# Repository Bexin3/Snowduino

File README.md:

# Snowduino
Want to get your own PCB? These files are all you need (untested)

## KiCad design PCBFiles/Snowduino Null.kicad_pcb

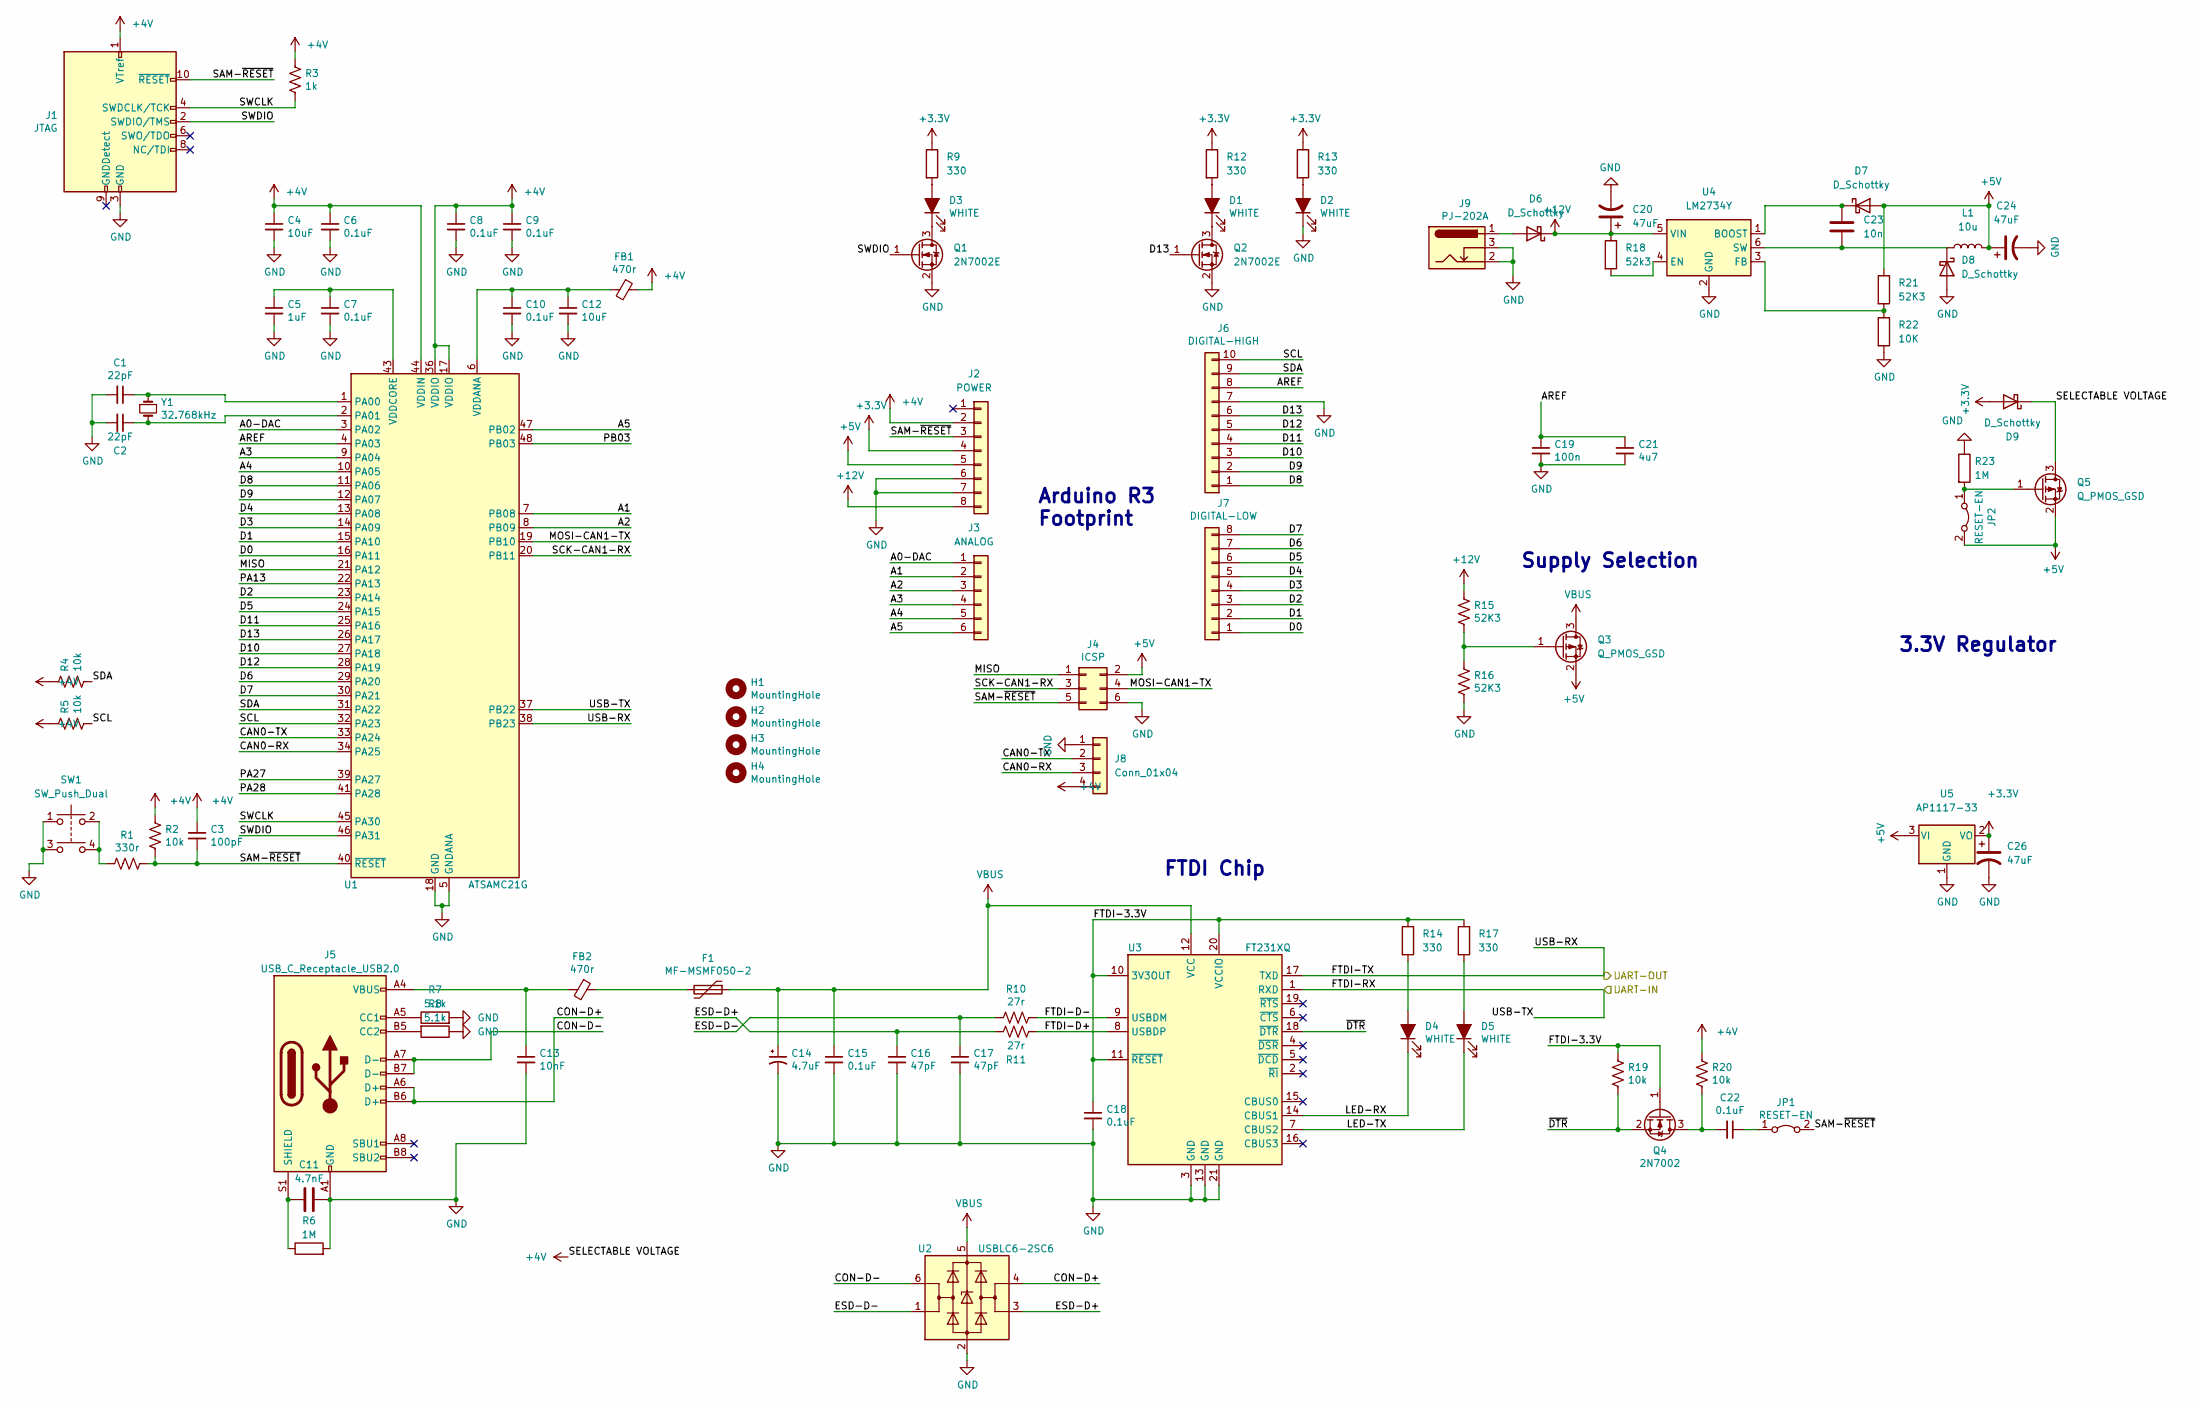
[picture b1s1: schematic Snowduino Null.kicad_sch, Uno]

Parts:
C1, C2: 22pF; C_0603_1608Metric
C3: 100pF; C_0603_1608Metric
C4, C12: 10uF; C_0805_2012Metric
C5: 1uF; C_0805_2012Metric
C6, C7, C8, C9, C10, C15, C18, C22: 0.1uF; C_0603_1608Metric
C11: 4.7nF; C_0603_1608Metric
C13: 10nF; C_0603_1608Metric
C14: 4.7uF; C_0805_2012Metric
C16, C17: 47pF; C_0603_1608Metric
C19: 100n; C_0603_1608Metric
C20, C24, C26: 47uF; CP_Elec_6.3x3.9
C21: 4u7; C_0603_1608Metric
C23: 10n; C_0603_1608Metric
D1, D2, D3, D4, D5: WHITE; LED_0603_1608Metric
D6, D7, D8: D_Schottky; D_SOD-123F
D9: D_Schottky; D_SOD-323
F1: MF-MSMF050-2; Fuse_1812_4532Metric
FB1: 470r; R_0603_1608Metric
FB2: 470r; R_0603_1608Metric; Part Number BLM18PG471SN1; Digikey PN 490-5223-1-ND
H1, H2, H3, H4: MountingHole; MountingHole_3.2mm_M3
J1: JTAG; PinHeader_2x05_P1.27mm_Vertical
J2: POWER; PinSocket_1x08_P2.54mm_Vertical
J3: ANALOG; PinSocket_1x06_P2.54mm_Vertical
J4: ICSP; PinHeader_2x03_P2.54mm_Vertical
J5: USB_C_Receptacle_USB2.0; USB_C_Receptacle_HRO_TYPE-C-31-M-12
J6: DIGITAL-HIGH; PinSocket_1x10_P2.54mm_Vertical
J7: DIGITAL-LOW; PinSocket_1x08_P2.54mm_Vertical
J8: Conn_01x04; PinHeader_1x04_P2.54mm_Vertical
J9: PJ-202A; DC005G25A20
JP1: RESET-EN; SolderJumper-2_P1.3mm_Bridged_RoundedPad1.0x1.5mm
JP2: RESET-EN; PinHeader_1x02_P1.27mm_Vertical
L1: 10u; L_6.3x6.3_H3
Q1, Q2: 2N7002E; SOT-23
Q3, Q5: Q_PMOS_GSD; SOT-23
Q4: 2N7002; SOT-23
R1: 330r; R_0603_1608Metric
R2, R4, R5, R19, R20: 10k; R_0603_1608Metric
R3: 1k; R_0603_1608Metric
R6, R23: 1M; R_0603_1608Metric
R7, R8: 5.1k; R_0603_1608Metric
R9, R12, R13, R14, R17: 330; R_0603_1608Metric
R10, R11: 27r; R_0603_1608Metric
R15, R16, R21: 52K3; R_0603_1608Metric
R18: 52k3; R_0603_1608Metric
R22: 10K; R_0603_1608Metric
SW1: SW_Push_Dual; PTS641SM31SMTR2LFS
U1: ATSAMC21G; TQFP-48_7x7mm_P0.5mm
U2: USBLC6-2SC6; SOT-23-6
U3: FT231XQ; QFN-20-1EP_4x4mm_P0.5mm_EP2.5x2.5mm
U4: LM2734Y; TSOT-23-6
U5: AP1117-33; SOT-223-3_TabPin2
Y1: 32.768kHz; Crystal_SMD_MicroCrystal_CC7V-T1A-2Pin_3.2x1.5mm

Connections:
+3V3: C26.1, D9.2 (A), J2.4, R9.1, R12.1, R13.1, U5.2 (VO)
+4V: C3.1, C4.1, C6.1, C8.1, C9.1, D9.1 (K), FB1.1, J1.1 (VTref), J2.2, J8.4, Q5.3 (D), R2.2, R3.1, R4.2, R5.2, R20.1, U1.17 (VDDIO), U1.36 (VDDIO), U1.44 (VDDIN)
+5V: C24.1, D7.2 (A), J2.5, J4.2, JP2.2 (B), L1.2, Q3.2 (S), Q5.2 (S), R21.1, U5.3 (VI)
+12V: C20.1, D6.1 (K), J2.8, R15.1, R18.1, U4.5 (VIN)
/A0-DAC: J3.1, U1.3 (PA02)
/A1: J3.2, U1.7 (PB08)
/A2: J3.3, U1.8 (PB09)
/A3: J3.4, U1.9 (PA04)
/A4: J3.5, U1.10 (PA05)
/A5: J3.6, U1.47 (PB02)
/AREF: C19.1, C21.1, J6.8, U1.4 (PA03)
/CAN0-RX: J8.3, U1.34 (PA25)
/CAN0-TX: J8.2, U1.33 (PA24)
/CON-D+: J5.A6 (D+), J5.B6 (D+), U2.4 (I/O2)
/CON-D-: J5.A7 (D-), J5.B7 (D-), U2.6 (I/O1)
/D0: J7.1, U1.16 (PA11)
/D1: J7.2, U1.15 (PA10)
/D2: J7.3, U1.23 (PA14)
/D3: J7.4, U1.14 (PA09)
/D4: J7.5, U1.13 (PA08)
/D5: J7.6, U1.24 (PA15)
/D6: J7.7, U1.29 (PA20)
/D7: J7.8, U1.30 (PA21)
/D8: J6.1, U1.11 (PA06)
/D9: J6.2, U1.12 (PA07)
/D10: J6.3, U1.27 (PA18)
/D11: J6.4, U1.25 (PA16)
/D12: J6.5, U1.28 (PA19)
/D13: J6.6, Q2.1 (G), U1.26 (PA17)
/ESD-D+: C16.1, R11.2, U2.3 (I/O2)
/ESD-D-: C17.1, R10.2, U2.1 (I/O1)
/FTDI-3.3V: C18.1, Q4.1 (G), R14.1, R17.1, R19.1, U3.10 (3V3OUT), U3.11 (~RESET), U3.20 (VCCIO)
/FTDI-D+: R11.1, U3.8 (USBDP)
/FTDI-D-: R10.1, U3.9 (USBDM)
/FTDI-RX: U1.37 (PB22), U3.1 (RXD)
/FTDI-TX: U1.38 (PB23), U3.17 (TXD)
/LED-RX: D4.1 (K), U3.14 (CBUS1)
/LED-TX: D5.1 (K), U3.7 (CBUS2)
/MISO: J4.1, U1.21 (PA12)
/MOSI-CAN1-TX: J4.4, U1.19 (PB10)
/PA13: U1.22 (PA13)
/PA27: U1.39 (PA27)
/PA28: U1.41 (PA28)
/PB03: U1.48 (PB03)
/SAM-~RESET: C3.2, J1.10 (~RESET), J2.3, J4.5, JP1.2 (B), R1.1, R2.1, U1.40 (~RESET)
/SCK-CAN1-RX: J4.3, U1.20 (PB11)
/SCL: J6.10, R5.1, U1.32 (PA23)
/SDA: J6.9, R4.1, U1.31 (PA22)
/SWCLK: J1.4 (SWDCLK/TCK), R3.2, U1.45 (PA30)
/SWDIO: J1.2 (SWDIO/TMS), Q1.1 (G), U1.46 (PA31)
/~DTR: Q4.2 (S), R19.2, U3.18 (~DTR)
GND: C1.2, C2.2, C4.2, C5.2, C6.2, C7.2, C8.2, C9.2, C10.2, C11.1, C12.2, C13.2, C14.2, C15.2, C16.2, C17.2, C18.2, C19.2, C20.2, C21.2, C24.2, C26.2, D2.1 (K), D8.2 (A), J1.3 (GND), J1.5 (GND), J2.6, J2.7, J4.6, J5.A1 (GND), J5.A12 (GND), J5.B1 (GND), J5.B12 (GND), J6.7, J8.1, J9.2, J9.3, Q1.2 (S), Q2.2 (S), R6.2, R7.2, R8.1, R16.2, R22.2, R23.1, SW1.1, SW1.3, U1.5 (GNDANA), U1.18 (GND), U1.35 (GND), U1.42 (GND), U2.2 (GND), U3.3 (GND), U3.13 (GND), U3.21 (GND), U4.2 (GND), U5.1 (GND)
unnamed: C1.1, U1.1 (PA00), Y1.1
unnamed: C2.1, U1.2 (PA01), Y1.2
unnamed: C5.1, C7.1, U1.43 (VDDCORE)
unnamed: C10.1, C12.1, FB1.2, U1.6 (VDDANA)
unnamed: C11.2, J5.S1 (SHIELD), R6.1
unnamed: C13.1, FB2.2, J5.A4 (VBUS), J5.A9 (VBUS), J5.B4 (VBUS), J5.B9 (VBUS)
unnamed: C22.1, JP1.1 (A)
unnamed: C22.2, Q4.3 (D), R20.2
unnamed: C23.1, D7.1 (K), U4.1 (BOOST)
unnamed: C23.2, D8.1 (K), L1.1, U4.6 (SW)
unnamed: D1.1 (K), Q2.3 (D)
unnamed: D1.2 (A), R12.2
unnamed: D2.2 (A), R13.2
unnamed: D3.1 (K), Q1.3 (D)
unnamed: D3.2 (A), R9.2
unnamed: D4.2 (A), R14.2
unnamed: D5.2 (A), R17.2
unnamed: D6.2 (A), J9.1
unnamed: F1.2, FB2.1
unnamed: J5.A5 (CC1), R7.1
unnamed: J5.B5 (CC2), R8.2
unnamed: JP2.1 (A), Q5.1 (G), R23.2
unnamed: Q3.1 (G), R15.2, R16.1
unnamed: R1.2, SW1.2, SW1.4
unnamed: R18.2, U4.4 (EN)
unnamed: R21.2, R22.1, U4.3 (FB)
VBUS: C14.1, C15.1, F1.1, Q3.3 (D), U2.5 (VBUS), U3.12 (VCC)

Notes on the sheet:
FTDI Chip
Arduino R3 Footprint
Supply Selection
3.3V Regulator

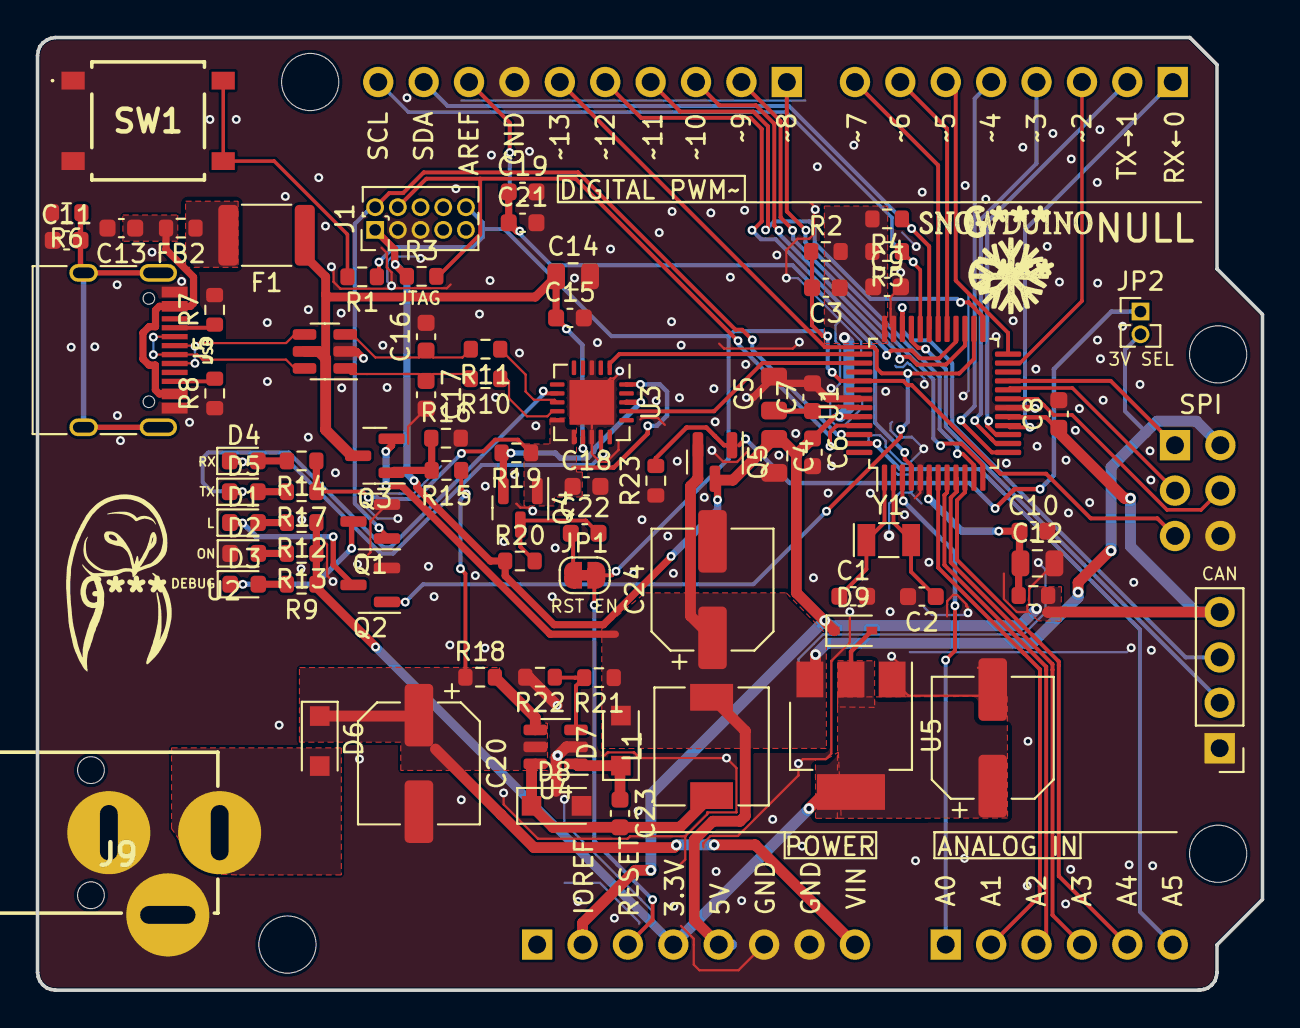
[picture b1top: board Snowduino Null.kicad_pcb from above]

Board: 2 copper layers, 68.5 x 53.3 mm, 88 parts (0 on the bottom side), 75 nets.

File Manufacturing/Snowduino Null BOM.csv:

Quantity;Reference;Footprint;Description;Manufacturer;Part number;Notes
2;C1,C2;C_0603_1608Metric;22pF;;0603N220J500;Can be replaced by another capacitator with white/black/gray color, same footprint and value, at leas 20V
1;C11;C_0603_1608Metric;4.7nF;;CGA3EAC0G2A472JT000E;Can be replaced by another capacitator with white/black/gray color, same footprint and value, at leas 20V
2;C13, C23;C_0603_1608Metric;10nF;;CC0603JRNPO9BN103;Can be replaced by another capacitator with white/black/gray color, same footprint and value, at leas 20V
1;C14;C_0805_2012Metric;4.7uF;;C0805B475K050T;Can be replaced by another capacitator with white/black/gray color, same footprint and value, at leas 20V
2;C16,C17;C_0603_1608Metric;47pF;;0603N470K500CT;Can be replaced by another capacitator with white/black/gray color, same footprint and value, at leas 20V
9;C19,C7,C18,C15,C8,C9,C6,C10,C22;C_0603_1608Metric;100nF;;0603B104J500CT;Can be replaced by another capacitator with white/black/gray color, same footprint and value, at leas 20V
3;C20,C26,C24;CP_Elec_6.3x3.9;47uF;;35CE47AX;Can be replaced by another capacitator with white/black/gray color, same footprint and value, at leas 20V
1;C21;Capacitor_SMD:C_0603_1608Metric;4.7uF;;TMK107BBJ475KA-T;Can be replaced by another capacitator with white/black/gray color, same footprint and value, at leas 20V
1;C3;C_0603_1608Metric;100pF;;CL10C101JB8NNNC;Can be replaced by another capacitator with white/black/gray color, same footprint and value, at leas 20V
2;C4,C12;C_0805_2012Metric;10uF;;CL21A106KAYNNNE;Can be replaced by another capacitator with white/black/gray color, same footprint and value, at leas 20V
1;C5;C_0805_2012Metric;1uF;;TMK212B7105KG-T;Can be replaced by another blue LED with 3.3v voltage and same footprint
5;D2,D3,D5,D4,D1;LED_0603_1608Metric;BLUE;Everlight;19-217/BHC-ZL1M2RY/3T;
3;D8,D6,D7;D_SOD-123F;D_Schottky;Onsemi;SS24FL;
1;D9;D_SOD-323;D_Schottky;Infineon;BAT60AE6327HTSA1;
1;F1;Fuse_1812_4532Metric;MF-MSMF050-2;;MF-MSMF050-2;
2;FB1,FB2;R_0603_1608Metric;470r;;BLM18PG471SN1D;
1;J1;PinHeader_2x05_P1.27mm_Vertical;JTAG;;DW127R-22-10-23;Any 10 pin JTAG male connector may be used
2;J2,J7;PinSocket_1x08_P2.54mm_Vertical;POWER;;KH-2.54FH-1X8P-H8.5;8*1 female connector with before mentioned specs, and same height as J6 J2 J7 and J3
1;J3;PinSocket_1x06_P2.54mm_Vertical;ANALOG;;KH-2.54FH-1X6P-H8.5;6*1 female connector with before mentioned specs, and same height as J6 J2 J7 and J3
1;J4;PinHeader_2x03_P2.54mm_Vertical;ICSP;ZHOURI;2.54-2*3;Male connector 
1;J5;USB_C_Receptacle_HRO_TYPE-C-31-M-12;USB_C_Receptacle_USB2.0;;TYPE-C-31-M-12;
1;J6;PinSocket_1x10_P2.54mm_Vertical;DIGITAL-HIGH;;KH-2.54FH-1X10P-H8.5;10*1 female connector with before mentioned specs, and same height as J6 J2 J7 and J3
1;J9;DC005G25A20;PJ-202A;;DC-005G-2.5A-2.0;Doesnt have to be the same part, but same dimensions and rated current 1A or higher
1;JP2;PinHeader_1x02_P1.27mm_Vertical;RESET-EN;;KH-1.27PH180-1X2P-L7.2;Vertical 1*2 male header, doesnt have to be the same but has to be same height as J1
1;L1;L_6.3x6.3_H3;10u;;YPRH0703-100M;Or another with identical footprint and specs
3;Q1,Q2,Q4;SOT-23;2N7002E;;2N7002;
2;Q3, Q5;SOT-23;Q_PMOS_GSD;;PMV48XP;
6;R1,R9,R14,R12,R13,R17;R_0603_1608Metric;330r;;0603WAF3300T5E;Can be replaced by another 0603 SMD resistor with same resistance
2;R10,R11;R_0603_1608Metric;27r;;0603WAF270JT5E;Can be replaced by another 0603 SMD resistor with same resistance
4;R18,R15,R16,R21;R_0603_1608Metric;52k3;;0603WAF5232T5E;Can be replaced by another 0603 SMD resistor with same resistance
6;R20,R22,R5,R2,R4,R19;R_0603_1608Metric;10k;;0603WAF1002T5E;Can be replaced by another 0603 SMD resistor with same resistance
2;R23,R6;R_0603_1608Metric;1M;;0603WAF1004T5E;Can be replaced by another 0603 SMD resistor with same resistance
1;R3;R_0603_1608Metric;1k;;0603WAF1001T5E;Can be replaced by another 0603 SMD resistor with same resistance
2;R7,R8;R_0603_1608Metric;5.1k;;0603WAF5101T5E;Can be replaced by another 0603 SMD resistor with same resistance
1;SW1;PTS641SM31SMTR2LFS;SW_SPST;;PTS641SM31SMTR2LFS;
1;U1;TQFP-48_7x7mm_P0.5mm;ATSAMC21G;Microchip;ATSAMC21G18A-AUT;Due to shortage may be harder to get, I am willing to pay extra if needed to be shipped from elsewhere
1;U2;SOT-23-6;USBLC6-2SC6;;USBLC6-2SC6;
1;U3;QFN-20-1EP_4x4mm_P0.5mm_EP2.5x2.5mm;FT231XQ;;FT231XQ-R;
1;U4;TSOT-23-6;LM2734Y;;LM2734YMK/NOPB;
1;U5;SOT-223-3_TabPin2;AP1117-33;;AMS1117-3.3;
1;Y1;Crystal_SMD_MicroCrystal_CC7V-T1A-2Pin_3.2x1.5mm;32.768kHz;;DST310S 32.768KHz;Or another same speced crystal
